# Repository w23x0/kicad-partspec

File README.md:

# kicad-partspec

**Pre-alpha.** Datasheet-derived PartSpec in, verified KiCad symbols and footprints out.

A model reads the datasheet and fills a PartSpec, a JSON file in which every value carries the datasheet page and a
verbatim quote. Deterministic code generates the KiCad files and checks them independently: against the spec, against
the PDF, and by loading them in `kicad-cli`.

The accuracy of model extraction has been measured on twenty-three parts in four small rounds, against answer keys written
and checked by models and not yet reviewed by a human. See
[evals/README.md](https://github.com/w23x0/kicad-partspec/blob/main/evals/README.md) before relying on it.

## Status

| Piece | State |
|---|---|
| PartSpec model, loader, spec-layer checks | done |
| Source check (quotes must appear on the cited datasheet page) | done |
| KiCad symbol generation (multi-unit, alternates, grid-aligned) | done |
| Symbol checks (pins vs spec, grid, overlap, name collisions) | done |
| `kicad-cli` load check | done |
| Footprint generation (dual-row and quad packages, exposed pad) from the datasheet land pattern | done |
| Footprint checks (pads vs datasheet, pads reach leads, silkscreen, courtyard) + `kicad-cli` load | done |
| MCP server (3 tools), skill, plugin manifests | done; loads with `claude --plugin-dir` (marketplace install not tested) |
| Extraction evaluation (`evals/score.py`, rounds 1 to 5 in `evals/runs/`) | done, 23 parts, 2 runs each |

## Install

Python 3.10 to 3.13.

```
pip install kicad-partspec            # CLI
pip install "kicad-partspec[mcp]"     # CLI + MCP server
```

To try the development version instead: `pip install "git+https://github.com/w23x0/kicad-partspec"`.

Optional tools the checks use when present: KiCad 9 or later (`kicad-cli`, for the load checks; without it you get a
warning instead) and poppler (`pdftotext`, for the datasheet quote check).

The package contains the CLI and the MCP server. The skill that teaches a model how to extract a PartSpec, and the plugin
manifests, live in the repository (`skills/`, `.claude-plugin/`, `.mcp.json`), not in the wheel.

## Use

```
kicad-partspec validate SPEC.json [--datasheet FILE.pdf]
kicad-partspec build SPEC.json --out DIR      # writes <mpn>.kicad_sym and <lib>.pretty/<name>.kicad_mod, verifies both
kicad-partspec verify SPEC.json --symbol FILE --footprint FILE
kicad-partspec-mcp                            # MCP server; PARTSPEC_WORKSPACE limits the paths it may touch
python evals/check_gold.py --datasheets DIR_WITH_PDFS
python evals/score.py --extracted DIR --datasheets DIR_WITH_PDFS   # score model extractions against gold
```

Add `--concise` to print failures in full and warnings only counted by kind.

Gold cases and their conventions are in `evals/README.md`. Generated symbols target the KiCad 9 file format
(version 20241209) and were loaded with KiCad 9.0.9.

Footprints are generated from the datasheet's example land pattern (`land_*` dimensions), not computed from a standard,
so a part whose datasheet has no land pattern gets a symbol and a `footprint.skipped` warning that names the missing
dimensions. Dual-row packages (SOIC, SOP, SSOP, TSSOP, MSOP, VSSOP, SOT-23 and TSOT-23) need an even pin count, and
quad packages (QFN, VQFN, WQFN, UQFN, QFP, TQFP, LQFP) a pin count divisible by 4; an odd-pin SOT-23 such as SOT-23-5
has unequal rows and is skipped with that reason.

## Repository workflow

`AGENTS.md` is the constitution every new agent session reads: the work loop, the red lines, and the gold-file arbitration
protocol. The only progress signal is the audit board:

```
./scripts/audit.sh [--datasheets DIR_WITH_PDFS]
```

It prints the rule counts (total, covered, passing, failing, regressed, uncovered) from `spec/rules.json` plus three gold
suites (`gold-spec`, `gold-quotes`, `gold-build`), and exits non-zero when a rule fails, a rule regresses, or a suite is
not green. The datasheet PDFs are not stored here; without them the quote layer reports `skipped` and does not decide the
exit status. An unattended loop drives one work cycle per round against that board (`scripts/loop.sh`); the round and
independent-audit prompts are in `scripts/prompts/`.

## History

This repository replaces `codex-kicad-mcp`, a read-first MCP server for KiCad projects. Its code is kept in the history
and on the `legacy` branch; the tags `v0.2.0` and `v0.2.1` point at it.

## License

MIT.

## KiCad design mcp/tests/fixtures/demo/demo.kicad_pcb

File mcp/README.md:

# codex-kicad-mcp

A safe, read-first [Model Context Protocol](https://modelcontextprotocol.io/)
server for KiCad workflows. It discovers KiCad projects, parses schematics and
PCBs into structured data, and runs ERC/DRC checks through `kicad-cli` without
editing design files. MCP resources expose the same data through stable URIs,
prompts provide structured task instructions, and an opt-in write API performs
snapshot-backed, audited minimal edits.

## Install

```bash
uv pip install codex-kicad-mcp
```

Or from a source checkout:

```bash
cd mcp
uv pip install -e ".[dev]"
```

## Run

Set `KICAD_WORKSPACE` to the directory that contains your `.kicad_pro`
projects, then start the stdio server:

```bash
export KICAD_WORKSPACE="/path/to/eda-workspace"
codex-kicad-mcp
```

On Windows PowerShell use
`$env:KICAD_WORKSPACE = "C:/path/to/eda-workspace"` instead. Forward-slash
paths work on every platform.

Every tool resolves paths below `KICAD_WORKSPACE`; attempts to escape fail
before any file access or command runs. See
[`docs/security-model.md`](../docs/security-model.md) for the full trust
boundaries.

## Tools

| Tool | Reads | KiCad required |
| --- | --- | --- |
| `kicad_cli_version` | CLI version | Yes |
| `list_kicad_projects` | Workspace tree | No |
| `inspect_project` | Project file inventory | No |
| `project_summary` | Project JSON and inventory | No |
| `read_schematic` | Schematic S-expression | No |
| `read_pcb` | PCB S-expression | No |
| `read_hierarchy` | Sheet hierarchy and pins | No |
| `read_buses` | Bus geometry and entries | No |
| `read_netlist` | Netlist CLI export | Yes |
| `read_bom` | BOM CLI export | Yes |
| `read_board_metrics` | Board size and copper totals | No |
| `read_layer_stackup` | Stackup or layer table | No |
| `read_zones` | Copper zones and polygons | No |
| `read_vias` | Vias and layer pairs | No |
| `run_kicad_cli_check` | Structured ERC/DRC JSON | Yes |
| `analyze_power_rails` | Netlist power topology | Yes |
| `check_decoupling` | Netlist and PCB capacitor placement | Yes |
| `cross_probe` | Schematic, netlist, and PCB matches | Yes |
| `compare_schematic_pcb` | Netlist-to-PCB parity | Yes |
| `run_design_review` | Unified review findings | Yes |
| `analyze_signal_integrity` | PCB routing geometry | No |
| `analyze_board_density` | PCB occupancy metrics | No |
| `check_fabrication_readiness` | PCB manufacturing readiness | No |
| `preview_write` | Dry-run edit plan (opt-in) | No |
| `confirm_write` | Execute previewed edit (opt-in) | No |
| `rollback_snapshot` | Restore snapshot files (opt-in) | No |
| `list_snapshots` | Write snapshot inventory (opt-in) | No |
| `get_write_audit` | Append-only audit log (opt-in) | No |

Write tools are inert unless `KICAD_ENABLE_WRITES=1` is set exactly; see
[`docs/tool-reference.md`](../docs/tool-reference.md) for the preview →
confirm pipeline, token binding, and audit record shape.

## Resources

Nine resources under `codex-kicad://projects/{project}/…` mirror the read
tools: `manifest`, `raw` (suffix allowlist, size-bounded), `schematic`, `pcb`,
`hierarchy`, `netlist`, `bom`, `stackup`, and `report` (normalized local
ERC/DRC JSON). The `{project}` parameter is the percent-encoded
workspace-relative `.kicad_pro` path.

## Prompts

Seven prompts render structured task instructions (never writes):
`audit_project`, `generate_bom_report`, `review_power_distribution`,
`review_signal_integrity`, `cross_probe_issue`, `prepare_fabrication`, and
`summarize_project_for_handoff`.

## Configuration

All limits are read at call time; invalid values raise a tool error instead of
being clamped.

| Variable | Default | Purpose |
| --- | --- | --- |
| `KICAD_WORKSPACE` | — (required) | Root directory for all project paths |
| `KICAD_MAX_FILE_BYTES` | 33554432 | Largest artifact accepted for parsing |
| `KICAD_MAX_SEXPR_TOKENS` | 1000000 | S-expression token budget |
| `KICAD_MAX_SEXPR_DEPTH` | 512 | S-expression nesting budget |
| `KICAD_MAX_RESULT_ITEMS` | 100000 | Item cap per response |
| `KICAD_MAX_CLI_OUTPUT_BYTES` | 1048576 | CLI stdout/stderr cap per response |
| `KICAD_CLI_VERSION_TIMEOUT` | 15 | Seconds for `kicad-cli --version` |
| `KICAD_CLI_CHECK_TIMEOUT` | 120 | Seconds for an ERC/DRC check |
| `KICAD_EXPORT_TIMEOUT` | 120 | Seconds for a netlist or BOM export |
| `KICAD_ENABLE_WRITES` | unset (writes off) | Set exactly `1` to enable the write API |
| `KICAD_SNAPSHOT_ROOT` | `<workspace>/.kicad-mcp-snapshots` | Directory for write snapshots and audit log |
| `KICAD_WRITE_TOKEN_TTL` | 900 | Confirm-token lifetime in seconds |
| `KICAD_WRITE_PREVIEW_TTL` | 1800 | Preview plan lifetime in seconds |
| `KICAD_MAX_SNAPSHOTS_LISTED` | 50 | Cap on `list_snapshots` results |

The complete tool contract lives in
[`docs/tool-reference.md`](../docs/tool-reference.md).

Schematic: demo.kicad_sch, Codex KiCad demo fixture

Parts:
C1: 100nF
C2: 10uF
R1: 10k
U1: MCU_8PIN; SOIC-8_3.9x4.9mm_P1.27mm

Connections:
CLK: U1.3 (CLK)
D0: U1.4 (D0)
D1: U1.5 (D1)
GND: C1.2, C2.2, U1.2 (GND)
RST: R1.2, U1.6 (RST)
VCC: C2.1, U1.1 (VDD)

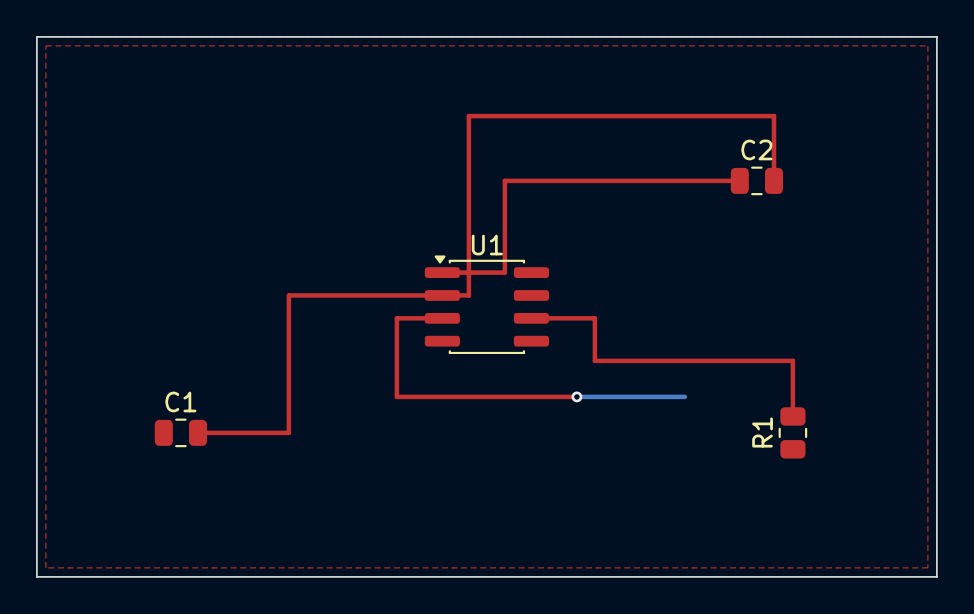
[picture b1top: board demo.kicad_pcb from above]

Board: 2 copper layers, 50.0 x 30.0 mm, 4 parts (0 on the bottom side), 3 nets.
